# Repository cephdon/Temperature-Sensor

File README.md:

# Temperature-Sensor
_Author: Andres Garcia_

This Metamorphosys design project captures a simple temperature sensor circuit. A sensor on the board detects the ambient temperature, and a set of LEDs are illuminated to reflect the temperature being below, near, or above room temperature. This circuit is all analog and uses no digital components.

## Architecture

## Analysis
_what test benches to run, and what you'll see_

## Caveats
_assumptions, hacks, etc_

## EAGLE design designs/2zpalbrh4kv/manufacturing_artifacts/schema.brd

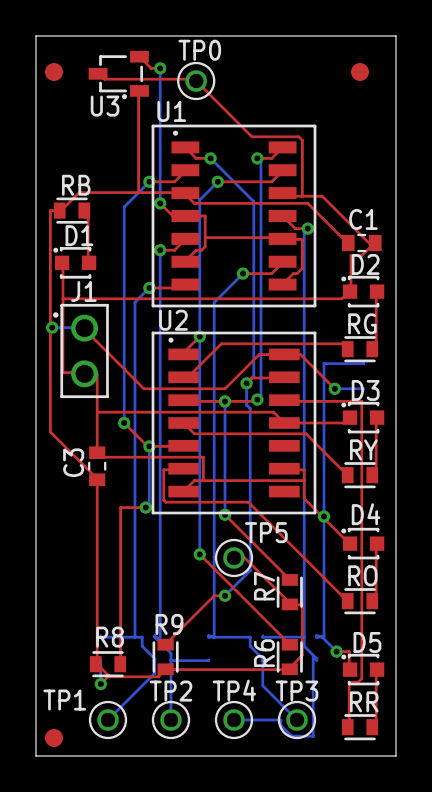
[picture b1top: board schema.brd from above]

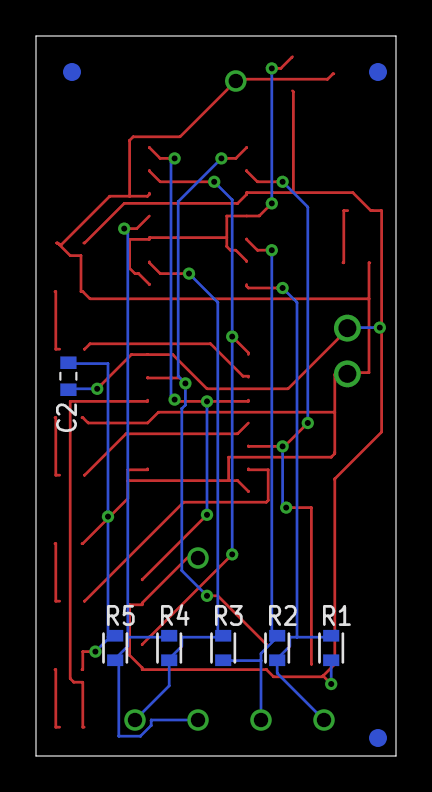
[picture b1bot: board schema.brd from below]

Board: 2 copper layers, 20.0 x 40.0 mm, 38 parts (9 on the bottom side), 20 nets.

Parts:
C1, C2, C3: C0603
D1, D2, D3, D4, D5: LED
FD1, FD2, FD3, FD4, FD5, FD6: FIDUCIAL1MM; FIDUCIAL_1MM
J1: 1X2-HEADER
R1, R2, R3, R4, R5, R6, R7, R8, R9: RESISTOR_0603; R_0603
RB: RESISTOR_0603; R_0603
RG: RESISTOR_0603; R_0603
RO: RESISTOR_0603; R_0603
RR: RESISTOR_0603; R_0603
RY: RESISTOR_0603; R_0603
TP0, TP1, TP2, TP3, TP4, TP5: TEST_POINT_VIA; TEST_POINT
U1: LM139_COMPARATOR; 14-SOIC
U2: 74VH14_INVERTER; 14-TSSOP
U3: MCP9700; 3-PIN_SOT_23

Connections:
unnamed: R6.P$2, U1.13, U2.1
unnamed: C1.1, C2.1, C3.1, J1.1, R1.P$1, R6.P$1, R7.P$1, R8.P$1, R9.P$1, RB.P$1, TP5.1, U1.3, U2.14, U3.VDD
unnamed: R7.P$2, U1.14, U2.3
unnamed: R8.P$2, U1.2, U2.5
unnamed: R9.P$2, U1.1, U2.13
unnamed: R1.P$2, R2.P$1, TP1.1, U1.7
unnamed: R3.P$2, R4.P$1, TP3.1, U1.9
unnamed: R4.P$2, R5.P$1, TP4.1, U1.11
unnamed: R2.P$2, R3.P$1, TP2.1, U1.5
unnamed: U1.4, U1.6, U1.8, U1.10, U3.VOUT
unnamed: C1.2, C2.2, C3.2, D1.CATHODE, D2.CATHODE, D3.CATHODE, D4.CATHODE, D5.CATHODE, J1.2, R5.P$2, TP0.1, U1.12, U2.7, U2.9, U2.11, U3.GND
unnamed: RR.P$1, U2.12
unnamed: RY.P$1, U2.4
unnamed: RO.P$1, U2.6
unnamed: RG.P$1, U2.2
unnamed: D2.ANODE, RG.P$2
unnamed: D3.ANODE, RY.P$2
unnamed: D4.ANODE, RO.P$2
unnamed: D5.ANODE, RR.P$2
unnamed: D1.ANODE, RB.P$2

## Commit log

2015-02-05 Initial model check-in
2015-02-19 Update from internal repo
2015-02-19 Organization improvement to ComponentAssemblies folder
2015-03-18 Use new range convention for RangeLayoutConstraints
2015-03-18 Update layout constraints to reflect new origin-centric scheme
2015-04-13 CT-40. Updated temp-sensor components that are in morph-component repo. Runs PnR test bench but fails. Addressing in CT-57.
